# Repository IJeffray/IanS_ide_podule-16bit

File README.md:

# IDE podule 16 bit

16-bit IDE podule for Acorn machines. It also includes a header for a CH376 USB module compatible with USBFS.

Compatibe with the interface number 0 version of ZIDEFS - https://www.zeridajh.org/software/zidefs/index.html

Flash can be programmed in-situ, so the chip can be soldered on-board without a socket.

More details on USBFS and a stand-alone USBFS podule here - https://codeberg.org/IanS/ch376_podule

The flash chip (SST39SF010) can be used in its entirety as a single 128K block with both switches turned on. It make more sense to treat it as four 32K chunks to allow the alternative version of the ZIDEFS software to be used. Using the different versions (ZIDEFS/IDEFS/SIDEFS) allows multiple podules to be installed in a single machine. Note that the ZIDEFS partitioning, deviceid and formatting tools only work with the ZIDEFS version. 

As well as fitting any Acorn machine with a normal podule backplane, it can also be fitted in an A3xx machine without a backplane. To fit it without a backplane, remove the jumper on JP3 and connect the spare red wire (+5V) from the power supply to the podule on J4. Then plug the podule directly into the motherboard. Do not try this with any other machines as the connector is the wrong way around. (In theory you can also do this with an original A440, *not* an A4xx/1, but as the A440 was sold with a backplane, it's unlikely this will be needed.)

PCB

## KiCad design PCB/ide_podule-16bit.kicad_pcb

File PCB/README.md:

# ide podule 16bit

These are the KiCad (version 8) files for the 16-bit ide podule.

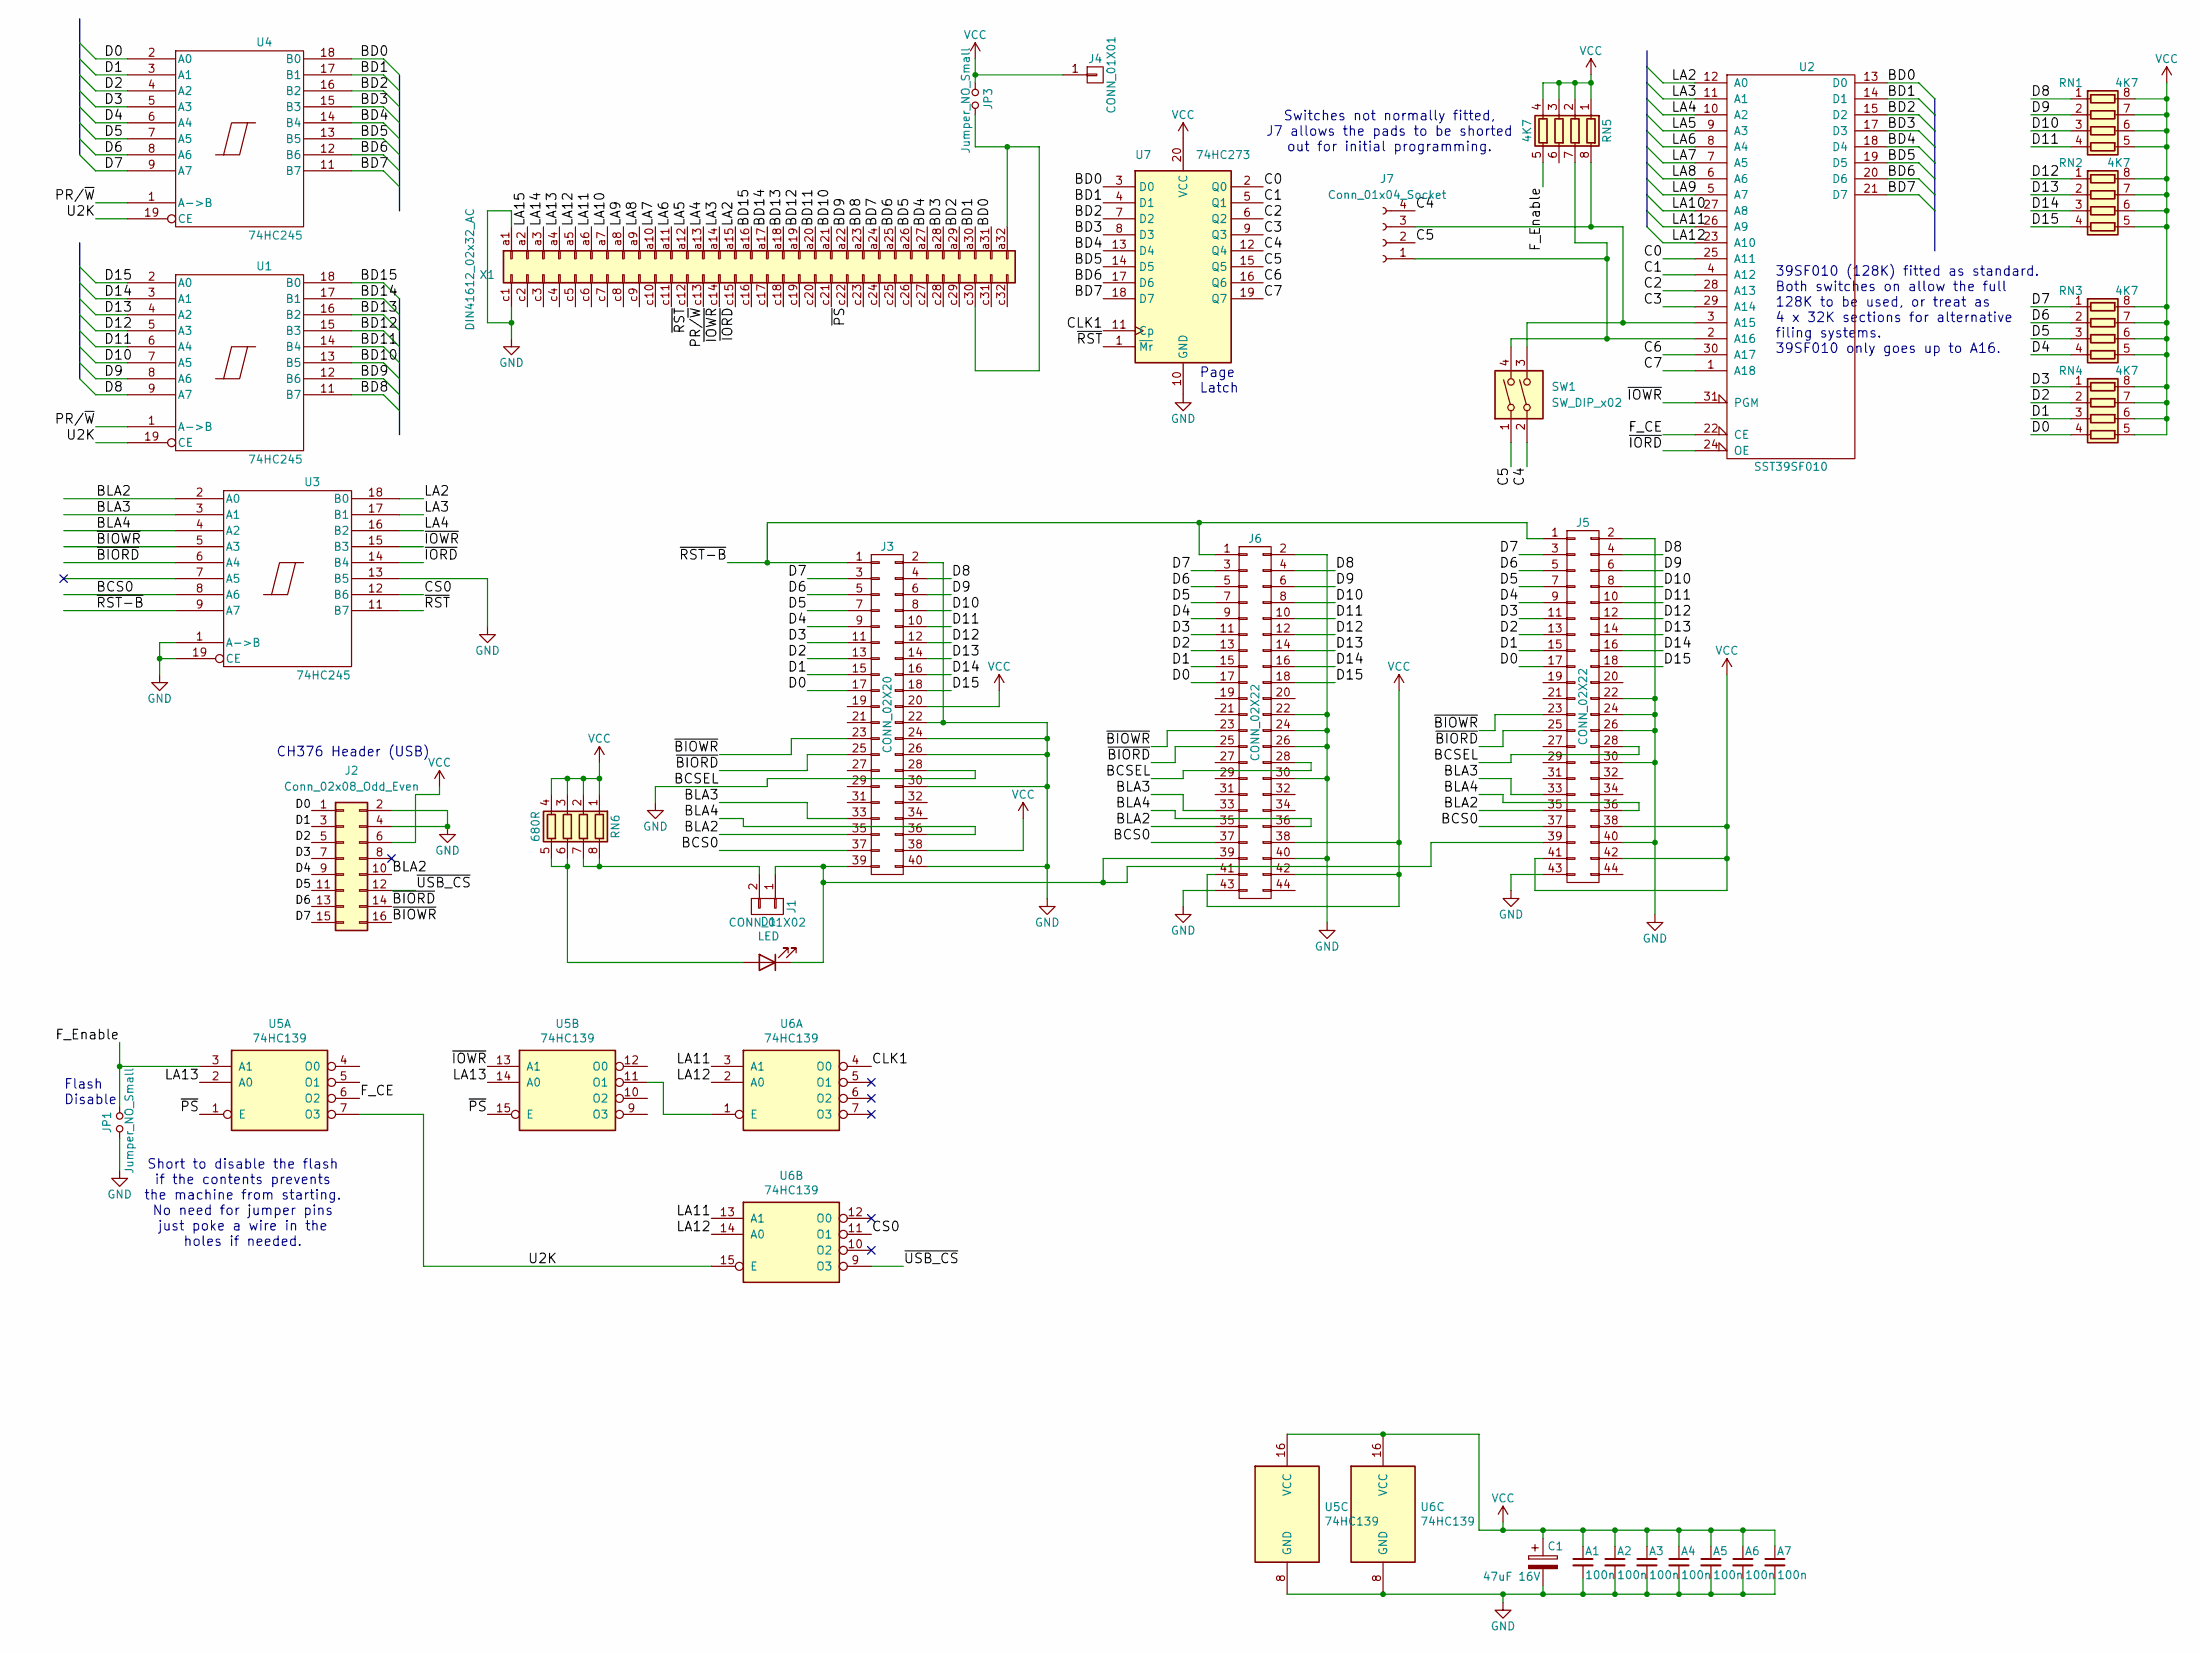
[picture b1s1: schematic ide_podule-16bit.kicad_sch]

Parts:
A1, A2, A3, A4, A5, A6, A7: 100n; C_1206_3216Metric_Pad1.33x1.80mm_HandSolder
C1: 47uF 16V; CP_Elec_6.3x5.8
D1: LED; LED_1206_3216Metric
J1: CONN_01X02; PinHeader_1x02_P2.54mm_Vertical
J2: Conn_02x08_Odd_Even; CH376-mod
J3: CONN_02X20; PinHeader_2x20_P2.54mm_Vertical
J4: CONN_01X01; SolderWirePad_2x_1-5mmDrill
J5: CONN_02X22; PinHeader_2x22_P2.00mm_Vertical
J6: CONN_02X22; IDE-edge-44pinC
J7: Conn_01x04_Socket; 4 way edge
JP1: Jumper_NO_Small; PinHeader_1x02_P2.54mm_Vertical
JP3: Jumper_NO_Small; PinHeader_2x01_P2.54mm_Vertical
RN1, RN2, RN3, RN4, RN5: 4K7; R_Array_Convex_4x0603
RN6: 680R; R_Array_Convex_4x0603
SW1: SW_DIP_x02; DIP-4_W7.62mm_Socket
U1, U3, U4: 74HC245; SOIC-20W_7.5x12.8mm_P1.27mm
U2: SST39SF010; PLCC-32_11.4x14.0mm_P1.27mm
U5, U6: 74HC139; STC_SOP-16_3.9x9.9mm_P1.27mm
U7: 74HC273; SOIC-20W_7.5x12.8mm_P1.27mm
X1: DIN41612_02x32_AC; DIN41612_C_2x32_Male_Horizontal_THT

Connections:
/BCS0: J3.37, J5.37, J6.37, U3.8 (A6)
/BD0: U2.13 (D0), U4.18 (B0), U7.3 (D0), X1.a31
/BD1: U2.14 (D1), U4.17 (B1), U7.4 (D1), X1.a30
/BD2: U2.15 (D2), U4.16 (B2), U7.7 (D2), X1.a29
/BD3: U2.17 (D3), U4.15 (B3), U7.8 (D3), X1.a28
/BD4: U2.18 (D4), U4.14 (B4), U7.13 (D4), X1.a27
/BD5: U2.19 (D5), U4.13 (B5), U7.14 (D5), X1.a26
/BD6: U2.20 (D6), U4.12 (B6), U7.17 (D6), X1.a25
/BD7: U2.21 (D7), U4.11 (B7), U7.18 (D7), X1.a24
/BD8: U1.11 (B7), X1.a23
/BD9: U1.12 (B6), X1.a22
/BD10: U1.13 (B5), X1.a21
/BD11: U1.14 (B4), X1.a20
/BD12: U1.15 (B3), X1.a19
/BD13: U1.16 (B2), X1.a18
/BD14: U1.17 (B1), X1.a17
/BD15: U1.18 (B0), X1.a16
/BLA2: J2.10, J3.35, J5.35, J6.35, U3.2 (A0)
/BLA3: J3.33, J5.33, J6.33, U3.3 (A1)
/BLA4: J3.36, J5.36, J6.36, U3.4 (A2)
/C0: U2.25 (A11), U7.2 (Q0)
/C1: U2.4 (A12), U7.5 (Q1)
/C2: U2.28 (A13), U7.6 (Q2)
/C3: U2.29 (A14), U7.9 (Q3)
/C4: J7.4, SW1.2, U7.12 (Q4)
/C5: J7.2, SW1.1, U7.15 (Q5)
/C6: U2.30 (A17), U7.16 (Q6)
/C7: U2.1 (A18), U7.19 (Q7)
/CLK1: U6.4 (O0), U7.11 (Cp)
/CS0: U3.12 (B6), U6.11 (O1)
/D0: J2.1, J3.17, J5.17, J6.17, RN4.4 (R4.1), U4.2 (A0)
/D1: J2.3, J3.15, J5.15, J6.15, RN4.3 (R3.1), U4.3 (A1)
/D2: J2.5, J3.13, J5.13, J6.13, RN4.2 (R2.1), U4.4 (A2)
/D3: J2.7, J3.11, J5.11, J6.11, RN4.1 (R1.1), U4.5 (A3)
/D4: J2.9, J3.9, J5.9, J6.9, RN3.4 (R4.1), U4.6 (A4)
/D5: J2.11, J3.7, J5.7, J6.7, RN3.3 (R3.1), U4.7 (A5)
/D6: J2.13, J3.5, J5.5, J6.5, RN3.2 (R2.1), U4.8 (A6)
/D7: J2.15, J3.3, J5.3, J6.3, RN3.1 (R1.1), U4.9 (A7)
/D8: J3.4, J5.4, J6.4, RN1.1 (R1.1), U1.9 (A7)
/D9: J3.6, J5.6, J6.6, RN1.2 (R2.1), U1.8 (A6)
/D10: J3.8, J5.8, J6.8, RN1.3 (R3.1), U1.7 (A5)
/D11: J3.10, J5.10, J6.10, RN1.4 (R4.1), U1.6 (A4)
/D12: J3.12, J5.12, J6.12, RN2.1 (R1.1), U1.5 (A3)
/D13: J3.14, J5.14, J6.14, RN2.2 (R2.1), U1.4 (A2)
/D14: J3.16, J5.16, J6.16, RN2.3 (R3.1), U1.3 (A1)
/D15: J3.18, J5.18, J6.18, RN2.4 (R4.1), U1.2 (A0)
/F_CE: U2.22 (CE), U5.6 (O2)
/F_Enable: JP1.2, RN5.5 (R4.2), U5.3 (A1)
/LA2: U2.12 (A0), U3.18 (B0), X1.a15
/LA3: U2.11 (A1), U3.17 (B1), X1.a14
/LA4: U2.10 (A2), U3.16 (B2), X1.a13
/LA5: U2.9 (A3), X1.a12
/LA6: U2.8 (A4), X1.a11
/LA7: U2.7 (A5), X1.a10
/LA8: U2.6 (A6), X1.a9
/LA9: U2.5 (A7), X1.a8
/LA10: U2.27 (A8), X1.a7
/LA11: U2.26 (A9), U6.3 (A1), U6.13 (A1), X1.a6
/LA12: U2.23 (A10), U6.2 (A0), U6.14 (A0), X1.a5
/LA13: U5.2 (A0), U5.14 (A0), X1.a4
/LA14: X1.a3
/LA15: X1.a2
/PR/~W: U1.1 (A->B), U4.1 (A->B), X1.c13
/U2K: U1.19 (CE), U4.19 (CE), U5.7 (O3), U6.15 (E)
/~BIORD: J2.14, J3.25, J5.25, J6.25, U3.6 (A4)
/~BIOWR: J2.16, J3.23, J5.23, J6.23, U3.5 (A3)
/~IORD: U2.24 (OE), U3.14 (B4), X1.c15
/~IOWR: U2.31 (PGM), U3.15 (B3), U5.13 (A1), X1.c14
/~PS: U5.1 (E), U5.15 (E), X1.c22
/~RST-B: J3.1, J5.1, J6.1, U3.9 (A7)
/~RST: U3.11 (B7), U7.1 (~Mr), X1.c12
/~USB_CS: J2.12, U6.9 (O3)
GND: A1.2, A2.2, A3.2, A4.2, A5.2, A6.2, A7.2, C1.2, J2.2, J2.4, J3.2, J3.22, J3.24, J3.26, J3.28, J3.30, J3.40, J5.2, J5.22, J5.24, J5.26, J5.28, J5.30, J5.40, J5.43, J6.2, J6.22, J6.24, J6.26, J6.28, J6.30, J6.40, J6.43, JP1.1, U1.10 (GND), U2.16 (GND), U3.1 (A->B), U3.10 (GND), U3.13 (B5), U3.19 (CE), U4.10 (GND), U5.8 (GND), U6.8 (GND), U7.10 (GND), X1.a1, X1.c1
unnamed: D1.2 (A), RN6.5 (R4.2), RN6.6 (R3.2)
unnamed: D1.1 (K), J1.1, J3.39, J5.39, J6.39
unnamed: J1.2, RN6.7 (R2.2), RN6.8 (R1.2)
unnamed: J7.1, RN5.7 (R2.2), SW1.4, U2.2 (A16)
unnamed: J7.3, RN5.8 (R1.2), SW1.3, U2.3 (A15)
unnamed: U5.11 (O1), U6.1 (E)
unnamed: JP3.2, X1.a32, X1.c30
VCC: A1.1, A2.1, A3.1, A4.1, A5.1, A6.1, A7.1, C1.1, J2.6, J3.20, J3.38, J4.1, J5.38, J5.41, J5.42, J6.38, J6.41, J6.42, JP3.1, RN1.5 (R4.2), RN1.6 (R3.2), RN1.7 (R2.2), RN1.8 (R1.2), RN2.5 (R4.2), RN2.6 (R3.2), RN2.7 (R2.2), RN2.8 (R1.2), RN3.5 (R4.2), RN3.6 (R3.2), RN3.7 (R2.2), RN3.8 (R1.2), RN4.5 (R4.2), RN4.6 (R3.2), RN4.7 (R2.2), RN4.8 (R1.2), RN5.1 (R1.1), RN5.2 (R2.1), RN5.3 (R3.1), RN5.4 (R4.1), RN6.1 (R1.1), RN6.2 (R2.1), RN6.3 (R3.1), RN6.4 (R4.1), U1.20 (VCC), U2.32 (VCC), U3.20 (VCC), U4.20 (VCC), U5.16 (VCC), U6.16 (VCC), U7.20 (VCC)

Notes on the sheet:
Short to disable the flash if the contents prevents the machine from starting. No need for jumper pins just poke a wire in the holes if needed.
39SF010 (128K) fitted as standard. Both switches on allow the full 128K to be used, or treat as 4 x 32K sections for alternative filing systems. 39SF010 only goes up to A16.
Page Latch
CH376 Header (USB)
Flash Disable
Switches not normally fitted, J7 allows the pads to be shorted out for initial programming.

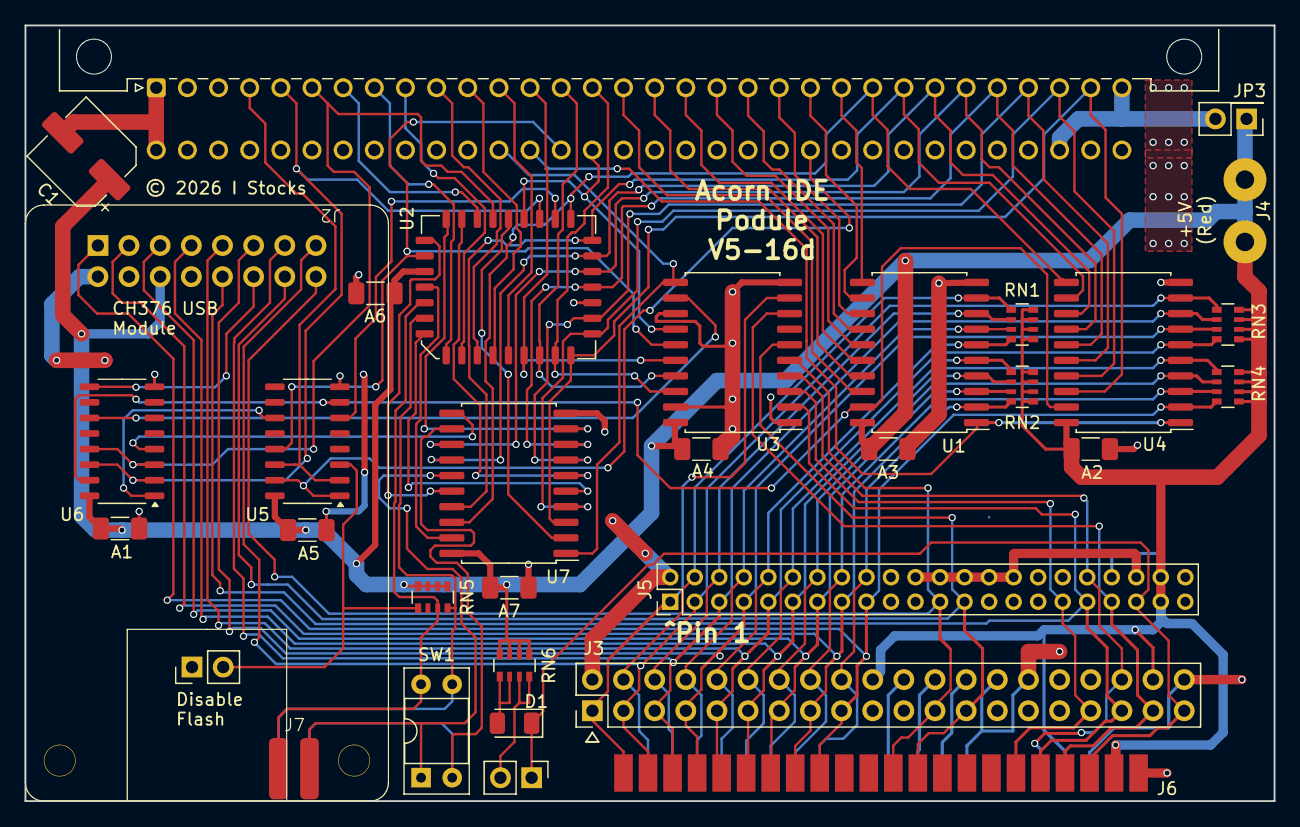
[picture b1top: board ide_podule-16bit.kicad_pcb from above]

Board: 2 copper layers, 101.9 x 63.2 mm, 33 parts (0 on the bottom side), 79 nets.

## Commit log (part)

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2026-04-19 initial version
2026-04-21 add software

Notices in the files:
PCB/ide_podule-16bit.kicad_pcb:
© 2026 I Stocks
